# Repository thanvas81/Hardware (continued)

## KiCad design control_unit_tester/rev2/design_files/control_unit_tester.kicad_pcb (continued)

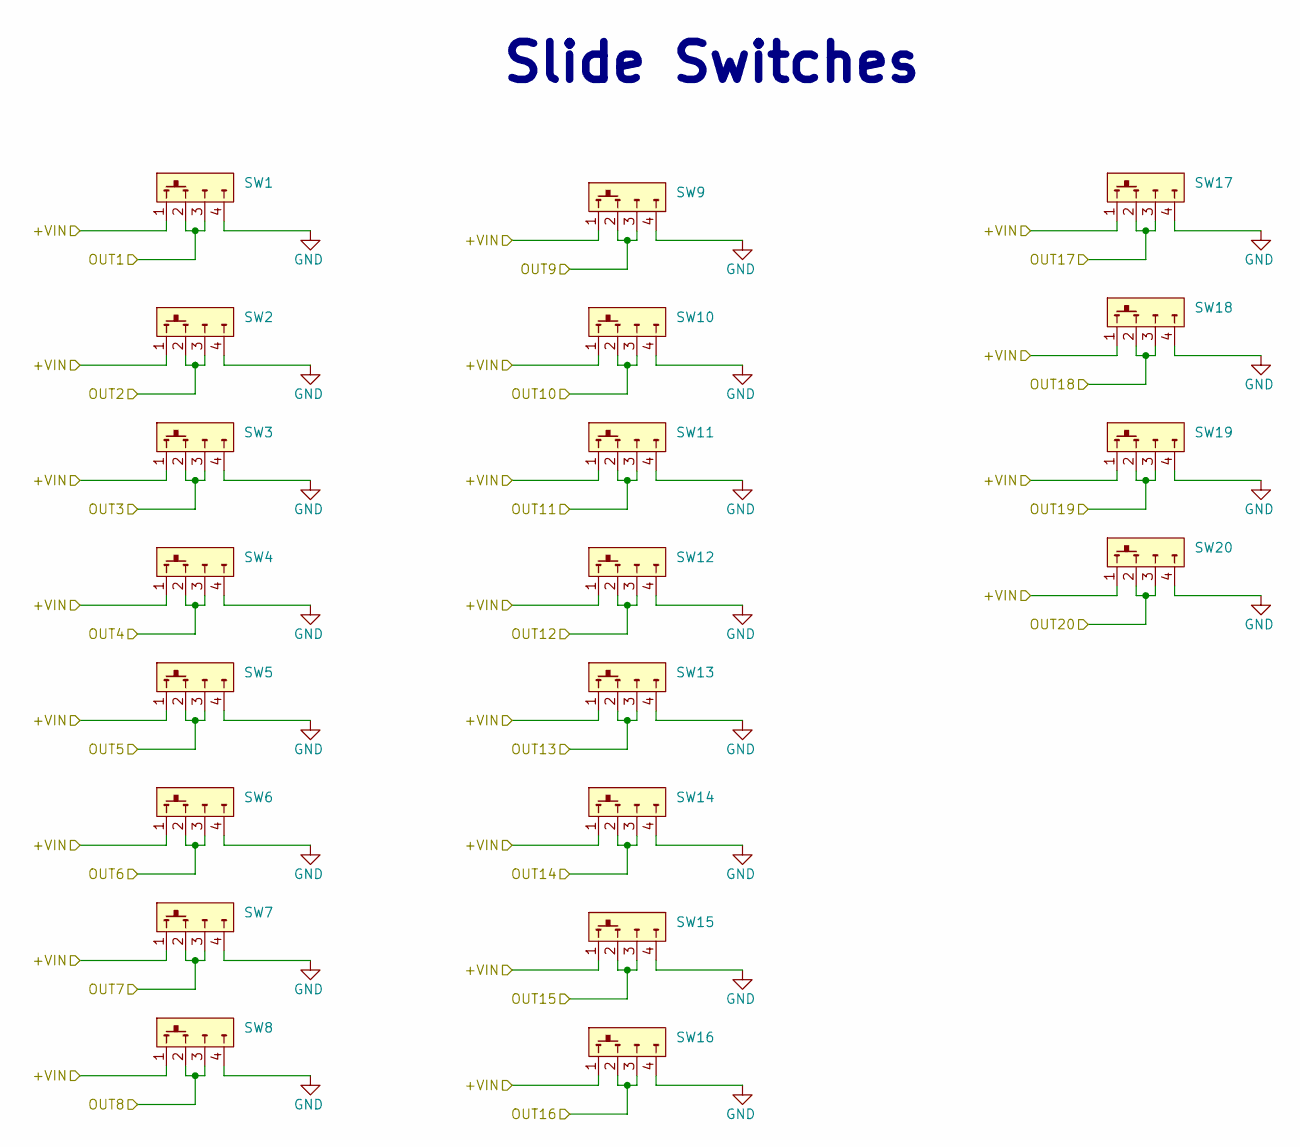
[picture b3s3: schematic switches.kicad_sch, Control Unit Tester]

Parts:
SW1, SW2, SW3, SW4, SW5, SW6, SW7, SW8, SW9, SW10, SW11, SW12, SW13, SW14, SW15, SW16, SW17, SW18, SW19, SW20: SLW-156646-5A-N-D

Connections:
+VIN: SW1.1, SW2.1, SW3.1, SW4.1, SW5.1, SW6.1, SW7.1, SW8.1, SW9.1, SW10.1, SW11.1, SW12.1, SW13.1, SW14.1, SW15.1, SW16.1, SW17.1, SW18.1, SW19.1, SW20.1; also elsewhere on the board
/OUT1: SW1.2, SW1.3; also elsewhere on the board
/OUT2: SW2.2, SW2.3; also elsewhere on the board
/OUT3: SW3.2, SW3.3; also elsewhere on the board
/OUT4: SW4.2, SW4.3; also elsewhere on the board
/OUT5: SW5.2, SW5.3; also elsewhere on the board
/OUT6: SW6.2, SW6.3; also elsewhere on the board
/OUT7: SW7.2, SW7.3; also elsewhere on the board
/OUT8: SW8.2, SW8.3; also elsewhere on the board
/OUT9: SW9.2, SW9.3; also elsewhere on the board
/OUT10: SW10.2, SW10.3; also elsewhere on the board
/OUT11: SW11.2, SW11.3; also elsewhere on the board
/OUT12: SW12.2, SW12.3; also elsewhere on the board
/OUT13: SW13.2, SW13.3; also elsewhere on the board
/OUT14: SW14.2, SW14.3; also elsewhere on the board
/OUT15: SW15.2, SW15.3; also elsewhere on the board
/OUT16: SW16.2, SW16.3; also elsewhere on the board
/OUT17: SW17.2, SW17.3; also elsewhere on the board
/OUT18: SW18.2, SW18.3; also elsewhere on the board
/OUT19: SW19.2, SW19.3; also elsewhere on the board
/OUT20: SW20.2, SW20.3; also elsewhere on the board
GND: SW1.4, SW2.4, SW3.4, SW4.4, SW5.4, SW6.4, SW7.4, SW8.4, SW9.4, SW10.4, SW11.4, SW12.4, SW13.4, SW14.4, SW15.4, SW16.4, SW17.4, SW18.4, SW19.4, SW20.4; also elsewhere on the board

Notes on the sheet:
Slide Switches

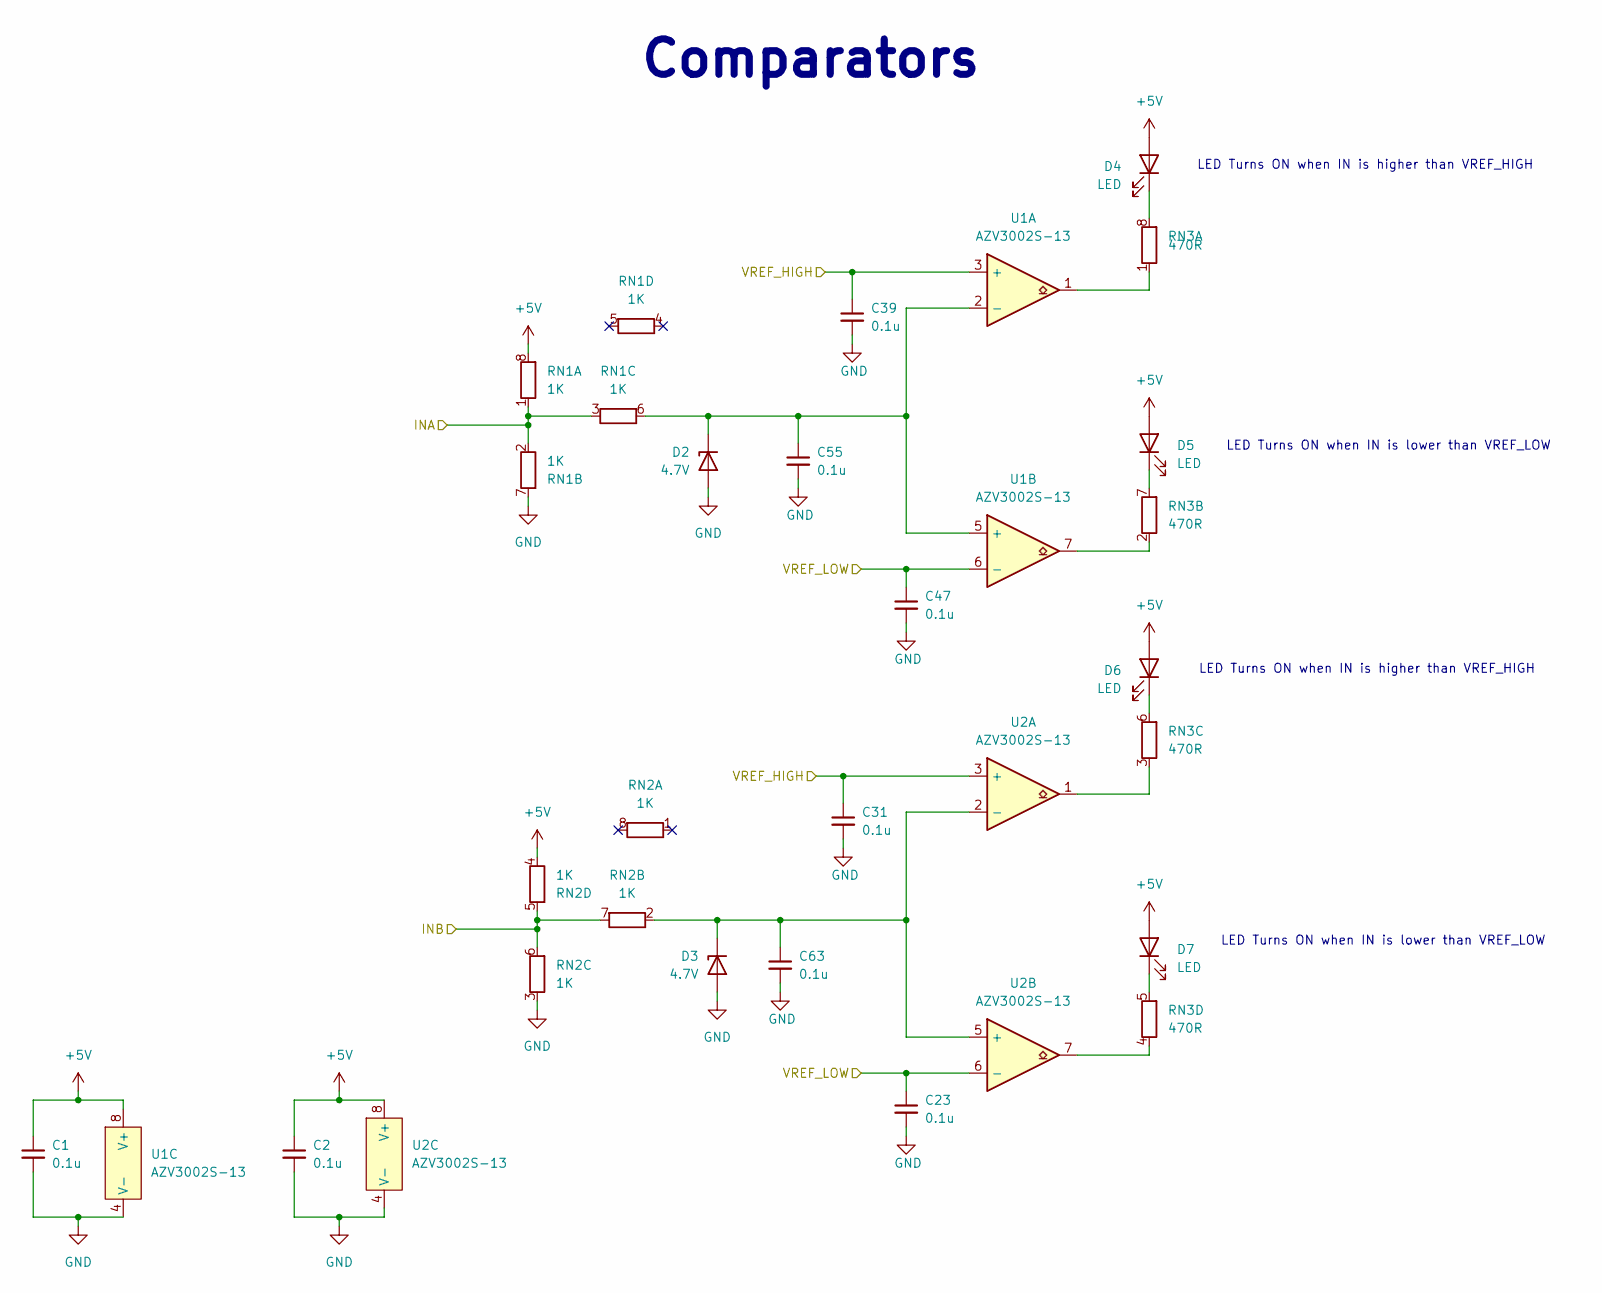
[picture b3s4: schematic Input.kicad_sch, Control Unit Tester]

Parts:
C1, C2, C23, C31, C39, C47, C55, C63: 0.1u; C_0603_1608Metric
D2, D3: 4.7V; D_SOD-123; PartNo MMSZ4688-HE3_A-08
D4, D5, D6, D7: LED; LED_0805_2012Metric
RN1, RN2: 1K; R_Array_Concave_4x0603
RN3: 470R; R_Array_Concave_4x0603
U1, U2: AZV3002S-13; SOIC-8_3.9x4.9mm_P1.27mm

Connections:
+5V: C1.1, C2.1, D4.2 (A), D5.2 (A), D6.2 (A), D7.2 (A), RN1.8 (R1.2), RN2.4 (R4.1), U1.8 (V+), U2.8 (V+); also elsewhere on the board
/IN1: RN1.1 (R1.1), RN1.2 (R2.1), RN1.3 (R3.1); also elsewhere on the board
/IN2: RN2.5 (R4.2), RN2.6 (R3.2), RN2.7 (R2.2); also elsewhere on the board
/VREF_HIGH: C31.1, C39.1, U1.3 (+), U2.3 (+); also elsewhere on the board
/VREF_LOW: C23.1, C47.1, U1.6 (-), U2.6 (-); also elsewhere on the board
GND: C1.2, C2.2, C23.2, C31.2, C39.2, C47.2, C55.2, C63.2, D2.2 (A), D3.2 (A), RN1.7 (R2.2), RN2.3 (R3.1), U1.4 (V-), U2.4 (V-); also elsewhere on the board
unnamed: C55.1, D2.1 (K), RN1.6 (R3.2), U1.2 (-), U1.5 (+)
unnamed: C63.1, D3.1 (K), RN2.2 (R2.1), U2.2 (-), U2.5 (+)
unnamed: D4.1 (K), RN3.8 (R1.2)
unnamed: D5.1 (K), RN3.7 (R2.2)
unnamed: D6.1 (K), RN3.6 (R3.2)
unnamed: D7.1 (K), RN3.5 (R4.2)
unnamed: RN3.1 (R1.1), U1.1
unnamed: RN3.2 (R2.1), U1.7
unnamed: RN3.3 (R3.1), U2.1
unnamed: RN3.4 (R4.1), U2.7

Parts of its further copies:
C3, C4, C5, C6, C7, C8, C9, C10, C11, C12, C13, C14, C15, C16, C24, C25, C26, C27, C28, C29, C30, C32, C33, C34, C35, C36, C37, C38, C40, C41, C42, C43, C44, C45, C46, C48, C49, C50, C51, C52, C53, C54, C56, C57, C58, C59, C60, C61, C62, C64, C65, C66, C67, C68, C69, C70: 0.1u; C_0603_1608Metric
D8, D9, D14, D15, D20, D21, D26, D27, D32, D33, D38, D39, D44, D45: 4.7V; D_SOD-123; PartNo MMSZ4688-HE3_A-08
D10, D11, D12, D13, D16, D17, D18, D19, D22, D23, D24, D25, D28, D29, D30, D31, D34, D35, D36, D37, D40, D41, D42, D43, D46, D47, D48, D49: LED; LED_0805_2012Metric
RN4, RN5, RN7, RN8, RN10, RN11, RN13, RN14, RN16, RN17, RN19, RN20, RN22, RN23: 1K; R_Array_Concave_4x0603
RN6, RN9, RN12, RN15, RN18, RN21, RN24: 470R; R_Array_Concave_4x0603
U3, U4, U5, U6, U7, U8, U9, U10, U11, U12, U13, U14, U15, U16: AZV3002S-13; SOIC-8_3.9x4.9mm_P1.27mm

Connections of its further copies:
+5V: C3.1, C4.1, C5.1, C6.1, C7.1, C8.1, C9.1, C10.1, C11.1, C12.1, C13.1, C14.1, C15.1, C16.1, D10.2 (A), D11.2 (A), D12.2 (A), D13.2 (A), D16.2 (A), D17.2 (A), D18.2 (A), D19.2 (A), D22.2 (A), D23.2 (A), D24.2 (A), D25.2 (A), D28.2 (A), D29.2 (A), D30.2 (A), D31.2 (A), D34.2 (A), D35.2 (A), D36.2 (A), D37.2 (A), D40.2 (A), D41.2 (A), D42.2 (A), D43.2 (A), D46.2 (A), D47.2 (A), D48.2 (A), D49.2 (A), RN4.8 (R1.2), RN5.4 (R4.1), RN7.8 (R1.2), RN8.4 (R4.1), RN10.8 (R1.2), RN11.4 (R4.1), RN13.8 (R1.2), RN14.4 (R4.1), RN16.8 (R1.2), RN17.4 (R4.1), RN19.8 (R1.2), RN20.4 (R4.1), RN22.8 (R1.2), RN23.4 (R4.1), U3.8 (V+), U4.8 (V+), U5.8 (V+), U6.8 (V+), U7.8 (V+), U8.8 (V+), U9.8 (V+), U10.8 (V+), U11.8 (V+), U12.8 (V+), U13.8 (V+), U14.8 (V+), U15.8 (V+), U16.8 (V+); also elsewhere on the board
/IN3: RN4.1 (R1.1), RN4.2 (R2.1), RN4.3 (R3.1); also elsewhere on the board
/IN4: RN5.5 (R4.2), RN5.6 (R3.2), RN5.7 (R2.2); also elsewhere on the board
/IN5: RN7.1 (R1.1), RN7.2 (R2.1), RN7.3 (R3.1); also elsewhere on the board
/IN6: RN8.5 (R4.2), RN8.6 (R3.2), RN8.7 (R2.2); also elsewhere on the board
/IN7: RN10.1 (R1.1), RN10.2 (R2.1), RN10.3 (R3.1); also elsewhere on the board
/IN8: RN11.5 (R4.2), RN11.6 (R3.2), RN11.7 (R2.2); also elsewhere on the board
/IN9: RN13.1 (R1.1), RN13.2 (R2.1), RN13.3 (R3.1); also elsewhere on the board
/IN10: RN14.5 (R4.2), RN14.6 (R3.2), RN14.7 (R2.2); also elsewhere on the board
/IN11: RN16.1 (R1.1), RN16.2 (R2.1), RN16.3 (R3.1); also elsewhere on the board
/IN12: RN17.5 (R4.2), RN17.6 (R3.2), RN17.7 (R2.2); also elsewhere on the board
/IN13: RN19.1 (R1.1), RN19.2 (R2.1), RN19.3 (R3.1); also elsewhere on the board
/IN14: RN20.5 (R4.2), RN20.6 (R3.2), RN20.7 (R2.2); also elsewhere on the board
/IN15: RN22.1 (R1.1), RN22.2 (R2.1), RN22.3 (R3.1); also elsewhere on the board
/IN16: RN23.5 (R4.2), RN23.6 (R3.2), RN23.7 (R2.2); also elsewhere on the board
/VREF_HIGH: C32.1, C33.1, C34.1, C35.1, C36.1, C37.1, C38.1, C40.1, C41.1, C42.1, C43.1, C44.1, C45.1, C46.1, U3.3 (+), U4.3 (+), U5.3 (+), U6.3 (+), U7.3 (+), U8.3 (+), U9.3 (+), U10.3 (+), U11.3 (+), U12.3 (+), U13.3 (+), U14.3 (+), U15.3 (+), U16.3 (+); also elsewhere on the board
/VREF_LOW: C24.1, C25.1, C26.1, C27.1, C28.1, C29.1, C30.1, C48.1, C49.1, C50.1, C51.1, C52.1, C53.1, C54.1, U3.6 (-), U4.6 (-), U5.6 (-), U6.6 (-), U7.6 (-), U8.6 (-), U9.6 (-), U10.6 (-), U11.6 (-), U12.6 (-), U13.6 (-), U14.6 (-), U15.6 (-), U16.6 (-); also elsewhere on the board
GND: C3.2, C4.2, C5.2, C6.2, C7.2, C8.2, C9.2, C10.2, C11.2, C12.2, C13.2, C14.2, C15.2, C16.2, C24.2, C25.2, C26.2, C27.2, C28.2, C29.2, C30.2, C32.2, C33.2, C34.2, C35.2, C36.2, C37.2, C38.2, C40.2, C41.2, C42.2, C43.2, C44.2, C45.2, C46.2, C48.2, C49.2, C50.2, C51.2, C52.2, C53.2, C54.2, C56.2, C57.2, C58.2, C59.2, C60.2, C61.2, C62.2, C64.2, C65.2, C66.2, C67.2, C68.2, C69.2, C70.2, D8.2 (A), D9.2 (A), D14.2 (A), D15.2 (A), D20.2 (A), D21.2 (A), D26.2 (A), D27.2 (A), D32.2 (A), D33.2 (A), D38.2 (A), D39.2 (A), D44.2 (A), D45.2 (A), RN4.7 (R2.2), RN5.3 (R3.1), RN7.7 (R2.2), RN8.3 (R3.1), RN10.7 (R2.2), RN11.3 (R3.1), RN13.7 (R2.2), RN14.3 (R3.1), RN16.7 (R2.2), RN17.3 (R3.1), RN19.7 (R2.2), RN20.3 (R3.1), RN22.7 (R2.2), RN23.3 (R3.1), U3.4 (V-), U4.4 (V-), U5.4 (V-), U6.4 (V-), U7.4 (V-), U8.4 (V-), U9.4 (V-), U10.4 (V-), U11.4 (V-), U12.4 (V-), U13.4 (V-), U14.4 (V-), U15.4 (V-), U16.4 (V-); also elsewhere on the board
unnamed: C56.1, D8.1 (K), RN4.6 (R3.2), U3.2 (-), U3.5 (+)
unnamed: C64.1, D9.1 (K), RN5.2 (R2.1), U4.2 (-), U4.5 (+)
unnamed: D10.1 (K), RN6.8 (R1.2)
unnamed: D11.1 (K), RN6.7 (R2.2)
unnamed: D12.1 (K), RN6.6 (R3.2)
unnamed: D13.1 (K), RN6.5 (R4.2)
unnamed: C57.1, D14.1 (K), RN7.6 (R3.2), U5.2 (-), U5.5 (+)
unnamed: C65.1, D15.1 (K), RN8.2 (R2.1), U6.2 (-), U6.5 (+)
unnamed: D16.1 (K), RN9.8 (R1.2)
unnamed: D17.1 (K), RN9.7 (R2.2)
unnamed: D18.1 (K), RN9.6 (R3.2)
unnamed: D19.1 (K), RN9.5 (R4.2)
unnamed: C58.1, D20.1 (K), RN10.6 (R3.2), U7.2 (-), U7.5 (+)
unnamed: C66.1, D21.1 (K), RN11.2 (R2.1), U8.2 (-), U8.5 (+)
unnamed: D22.1 (K), RN12.8 (R1.2)
unnamed: D23.1 (K), RN12.7 (R2.2)
unnamed: D24.1 (K), RN12.6 (R3.2)
unnamed: D25.1 (K), RN12.5 (R4.2)
unnamed: C59.1, D26.1 (K), RN13.6 (R3.2), U9.2 (-), U9.5 (+)
unnamed: C67.1, D27.1 (K), RN14.2 (R2.1), U10.2 (-), U10.5 (+)
unnamed: D28.1 (K), RN15.8 (R1.2)
unnamed: D29.1 (K), RN15.7 (R2.2)
unnamed: D30.1 (K), RN15.6 (R3.2)
unnamed: D31.1 (K), RN15.5 (R4.2)
unnamed: C60.1, D32.1 (K), RN16.6 (R3.2), U11.2 (-), U11.5 (+)
unnamed: C68.1, D33.1 (K), RN17.2 (R2.1), U12.2 (-), U12.5 (+)
unnamed: D34.1 (K), RN18.8 (R1.2)
unnamed: D35.1 (K), RN18.7 (R2.2)
unnamed: D36.1 (K), RN18.6 (R3.2)
unnamed: D37.1 (K), RN18.5 (R4.2)
unnamed: C61.1, D38.1 (K), RN19.6 (R3.2), U13.2 (-), U13.5 (+)
unnamed: C69.1, D39.1 (K), RN20.2 (R2.1), U14.2 (-), U14.5 (+)
unnamed: D40.1 (K), RN21.8 (R1.2)
unnamed: D41.1 (K), RN21.7 (R2.2)
unnamed: D42.1 (K), RN21.6 (R3.2)
unnamed: D43.1 (K), RN21.5 (R4.2)
unnamed: C62.1, D44.1 (K), RN22.6 (R3.2), U15.2 (-), U15.5 (+)
unnamed: C70.1, D45.1 (K), RN23.2 (R2.1), U16.2 (-), U16.5 (+)
unnamed: D46.1 (K), RN24.8 (R1.2)
unnamed: D47.1 (K), RN24.7 (R2.2)
unnamed: D48.1 (K), RN24.6 (R3.2)
unnamed: D49.1 (K), RN24.5 (R4.2)
unnamed: RN6.1 (R1.1), U3.1
unnamed: RN6.2 (R2.1), U3.7
unnamed: RN6.3 (R3.1), U4.1
unnamed: RN6.4 (R4.1), U4.7
unnamed: RN9.1 (R1.1), U5.1
unnamed: RN9.2 (R2.1), U5.7
unnamed: RN9.3 (R3.1), U6.1
unnamed: RN9.4 (R4.1), U6.7
unnamed: RN12.1 (R1.1), U7.1
unnamed: RN12.2 (R2.1), U7.7
unnamed: RN12.3 (R3.1), U8.1
unnamed: RN12.4 (R4.1), U8.7
unnamed: RN15.1 (R1.1), U9.1
unnamed: RN15.2 (R2.1), U9.7
unnamed: RN15.3 (R3.1), U10.1
unnamed: RN15.4 (R4.1), U10.7
unnamed: RN18.1 (R1.1), U11.1
unnamed: RN18.2 (R2.1), U11.7
unnamed: RN18.3 (R3.1), U12.1
unnamed: RN18.4 (R4.1), U12.7
unnamed: RN21.1 (R1.1), U13.1
unnamed: RN21.2 (R2.1), U13.7
unnamed: RN21.3 (R3.1), U14.1
unnamed: RN21.4 (R4.1), U14.7
unnamed: RN24.1 (R1.1), U15.1
unnamed: RN24.2 (R2.1), U15.7
unnamed: RN24.3 (R3.1), U16.1
unnamed: RN24.4 (R4.1), U16.7

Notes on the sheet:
LED Turns ON when IN is lower than VREF_LOW
Comparators
LED Turns ON when IN is higher than VREF_HIGH

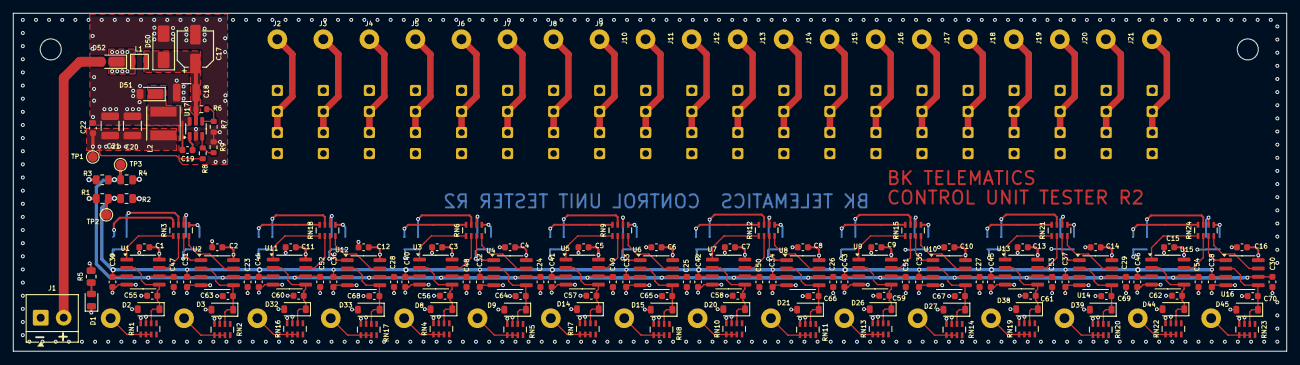
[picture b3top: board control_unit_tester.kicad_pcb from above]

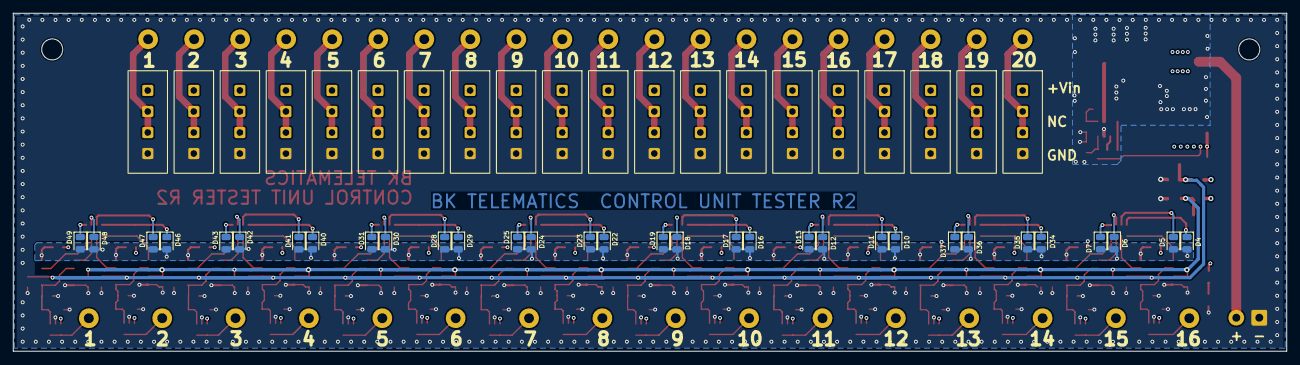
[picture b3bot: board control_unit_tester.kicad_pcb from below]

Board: 4 copper layers, 193.9 x 51.5 mm, 236 parts (52 on the bottom side), 128 nets.

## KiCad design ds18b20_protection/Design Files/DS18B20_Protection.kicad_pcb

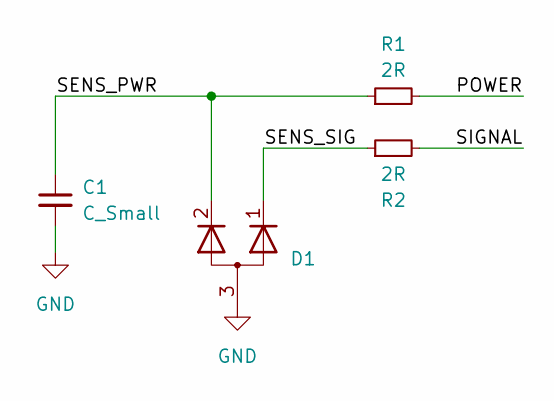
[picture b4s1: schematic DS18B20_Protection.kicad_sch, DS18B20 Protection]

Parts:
C1: C_Small; C_0805_2012Metric
D1: SOT-23
R1, R2: 2R; R_0805_2012Metric

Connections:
/POWER: R1.2
/SENS_PWR: C1.1, D1.2 (K), R1.1
/SENS_SIG: D1.1 (K), R2.1
/SIGNAL: R2.2
GND: C1.2, D1.3 (A)

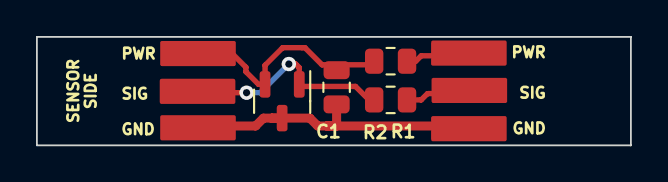
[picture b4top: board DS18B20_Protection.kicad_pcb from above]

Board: 11 copper layers, 33.0 x 6.0 mm, 4 parts (0 on the bottom side), 3 nets.

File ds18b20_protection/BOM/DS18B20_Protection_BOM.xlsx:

Reference | Value | Footprint | Qty
C1 | 1uF | Capacitor_SMD:C_0805_2012Metric | 1
D1 | gsot03c-g3-08 | Package_TO_SOT_SMD:SOT-23 | 1
R1,R2 | 1R | Resistor_SMD:R_0805_2012Metric | 2

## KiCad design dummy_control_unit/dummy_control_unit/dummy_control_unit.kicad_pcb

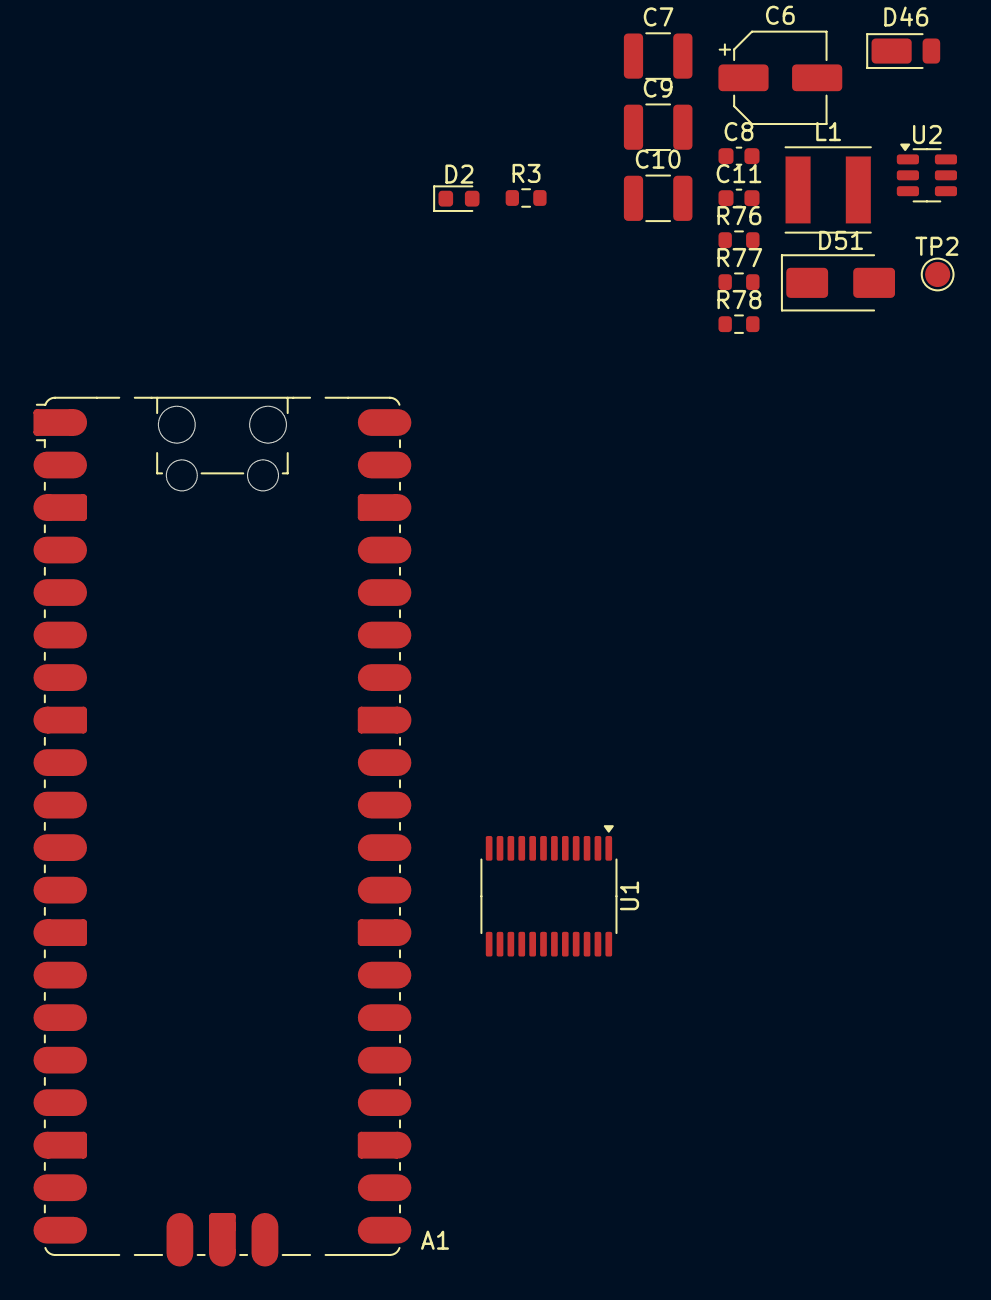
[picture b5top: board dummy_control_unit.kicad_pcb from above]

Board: 2 copper layers, 18 parts (0 on the bottom side), 11 nets, no tracks yet.

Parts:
A1: RaspberryPi_Pico; RaspberryPi_Pico_SMD_HandSolder
C6: 10u; CP_Elec_5x5.3
C7: 2.2u; C_1210_3225Metric
C8, C11: 0.1u; C_0603_1608Metric
C9, C10: 22u; C_1210_3225Metric
D2: LED_Small_Filled; LED_0603_1608Metric
D46: SBR3U60P1Q-7; D_PowerDI-123
D51: SMAJ40CAe3/TR13; D_SMA
L1: 22uH; L_Taiyo-Yuden_NR-50xx
R3: 470R; R_0603_1608Metric
R76: 100K; R_0603_1608Metric
R77: 33K; R_0603_1608Metric
R78: 10K; R_0603_1608Metric
TP2: TestPoint; TestPoint_Pad_D1.5mm
U1: PCA9555PW; TSSOP-24_4.4x7.8mm_P0.65mm
U2: LV2862x; SOT-23-6

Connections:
+3.3V: A1.39 (VSYS), C9.1, C10.1, C11.1, L1.2, R3.2, R77.2, TP2.1, U1.24 (VDD)
/power supply/+VIN_PROTECTED: C6.1, C7.1, D51.1 (K), R76.2, U2.5 (VIN)
/power supply/SW: C8.2, D46.1 (K), L1.1, U2.6 (SW)
GND: A1.3 (GND), A1.8 (GND), A1.13 (GND), A1.18 (GND), A1.23 (GND), A1.28 (GND), A1.33 (AGND), A1.38 (GND), A1.D2 (GND), C6.2, C7.2, C9.2, C10.2, C11.2, D2.1 (K), D46.2 (A), D51.2 (A), R78.1, U1.2 (A1), U1.3 (A2), U1.12 (VSS), U1.21 (A0), U2.2 (GND)
unnamed: A1.26 (GPIO20), U1.23 (SDA)
unnamed: A1.27 (GPIO21), U1.22 (SCL)
unnamed: A1.29 (GPIO22), U1.1 (~INT)
unnamed: D2.2 (A), R3.1
unnamed: C8.1, U2.1 (CB)
unnamed: R77.1, R78.2, U2.3 (FB)
unnamed: R76.1, U2.4 (~SHDN)

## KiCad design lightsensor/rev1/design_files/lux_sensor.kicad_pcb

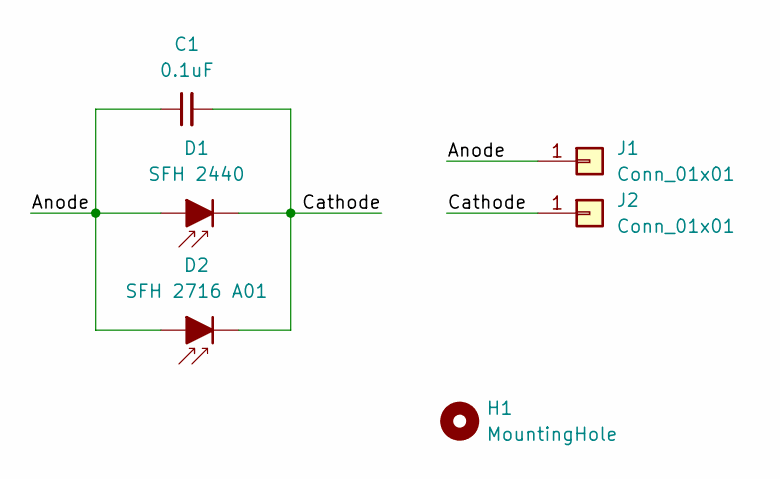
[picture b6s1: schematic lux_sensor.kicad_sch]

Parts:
C1: 0.1uF; C_0603_1608Metric
D1: SFH 2440
D2: SFH 2716 A01
H1: MountingHole; MountingHole_3.2mm_M3
J1, J2: Conn_01x01; pad_smd_3x6

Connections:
/Anode: C1.1, D1.2 (A), D2.2 (A), J1.1
/Cathode: C1.2, D1.1 (K), D2.1 (K), J2.1

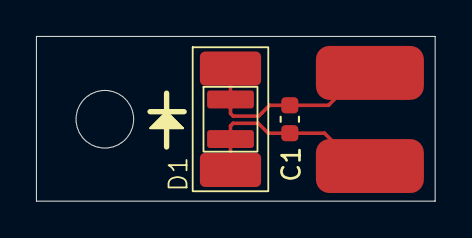
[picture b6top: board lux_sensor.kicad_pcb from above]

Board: 2 copper layers, 22.2 x 9.2 mm, 6 parts (0 on the bottom side), 2 nets.

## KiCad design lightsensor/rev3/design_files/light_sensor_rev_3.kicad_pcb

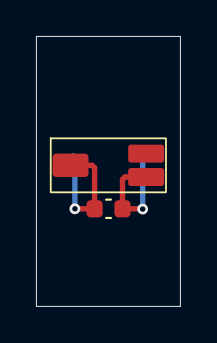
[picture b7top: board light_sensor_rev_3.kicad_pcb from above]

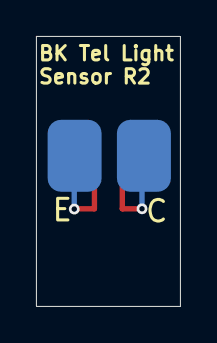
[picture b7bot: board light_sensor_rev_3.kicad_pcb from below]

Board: 2 copper layers, 8.0 x 15.0 mm, 4 parts (2 on the bottom side), 2 nets.

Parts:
C1: 0.1uF; C_0603_1608Metric
J3, J4: Conn_01x01; pad_smd_3x4
Q1: Q_Photo_NPN_EC; SFH-3410

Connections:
/Collector: C1.1, J3.1, Q1.2 (C)
/Emitter: C1.2, J4.1, Q1.1 (E)
